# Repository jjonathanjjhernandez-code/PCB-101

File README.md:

# PCB-101
Kicad Schematic/Gerber/PCB files for fututre projects!

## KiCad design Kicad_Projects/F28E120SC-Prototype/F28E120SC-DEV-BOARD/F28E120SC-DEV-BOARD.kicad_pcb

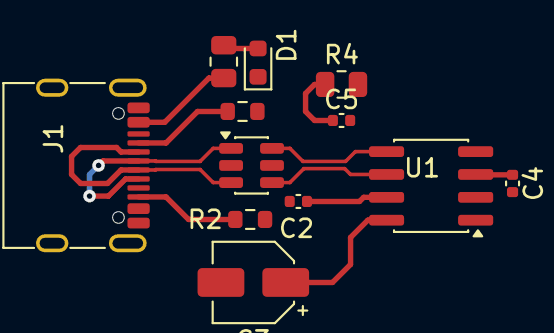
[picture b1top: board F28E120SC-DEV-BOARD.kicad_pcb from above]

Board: 2 copper layers, 16 parts (0 on the bottom side), 11 nets.

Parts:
C2, C4, C5: 0.1uF; C_0402_1005Metric
C3: 1uF; CP_Elec_4x5.4
D1: GREEN_LED; LED_0603_1608Metric
H1, H2, H3, H4: MountingHole; MountingHole_2.2mm_M2
J1: USB_C_Receptacle_USB2.0_16P; USB_C_Receptacle_G-Switch_GT-USB-7010ASV
R1, R4: 330; R_0805_2012Metric
R2, R3: 5.1k; R_0603_1608Metric
U1: HT42B534-2-Logical; SOIC-8_3.9x4.9mm_P1.27mm
U2: USBLC6-2SC6; SOT-23-6

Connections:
/D+: J1.A6 (D+), J1.B6 (D+), U1.5 (D+), U2.1 (I/O1), U2.6 (I/O1)
/D-: J1.A7 (D-), J1.B7 (D-), U1.6 (D-), U2.3 (I/O2), U2.4 (I/O2)
/DEVICE-POWER-MCU-POTENTIALLY: C4.1, U1.3 (VDDIO)
unnamed: D1.2 (A), R1.2
unnamed: J1.A5 (CC1), R3.2
unnamed: J1.B5 (CC2), R2.2
unnamed: C5.1, J1.SH (SHIELD), R4.1
unnamed: C3.1, U1.8 (V33O)
unnamed: C2.1, U1.7 (VDD)
unnamed: J1.A4 (VBUS), J1.A9 (VBUS), J1.B4 (VBUS), J1.B9 (VBUS), R1.1, U2.5 (VBUS)
USB-GND: C2.2, C3.2, C4.2, C5.2, D1.1 (K), J1.A1 (GND), J1.A12 (GND), J1.B1 (GND), J1.B12 (GND), R2.1, R3.1, R4.2, U1.1 (GND), U2.2 (GND)

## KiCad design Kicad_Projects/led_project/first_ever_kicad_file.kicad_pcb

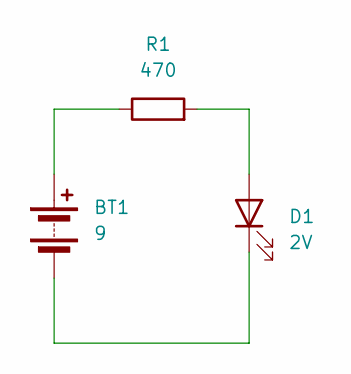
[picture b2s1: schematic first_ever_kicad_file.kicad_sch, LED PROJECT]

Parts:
BT1: 9; PinHeader_1x02_P2.54mm_Vertical
D1: 2V; LED_D5.0mm
R1: 470; R_Axial_DIN0207_L6.3mm_D2.5mm_P10.16mm_Horizontal

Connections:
unnamed: BT1.1 (+), R1.1
unnamed: BT1.2 (-), D1.1 (K)
unnamed: D1.2 (A), R1.2

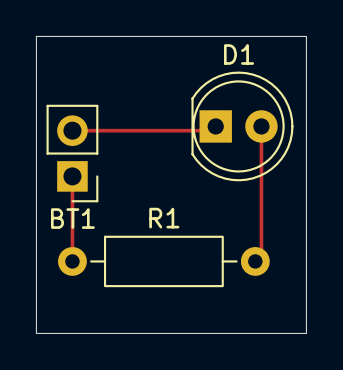
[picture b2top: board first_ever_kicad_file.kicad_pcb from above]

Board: 2 copper layers, 15.0 x 16.5 mm, 3 parts (0 on the bottom side), 3 nets.

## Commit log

2026-06-22 added some cool looking files!
2026-06-22 ltspice simulation files!
